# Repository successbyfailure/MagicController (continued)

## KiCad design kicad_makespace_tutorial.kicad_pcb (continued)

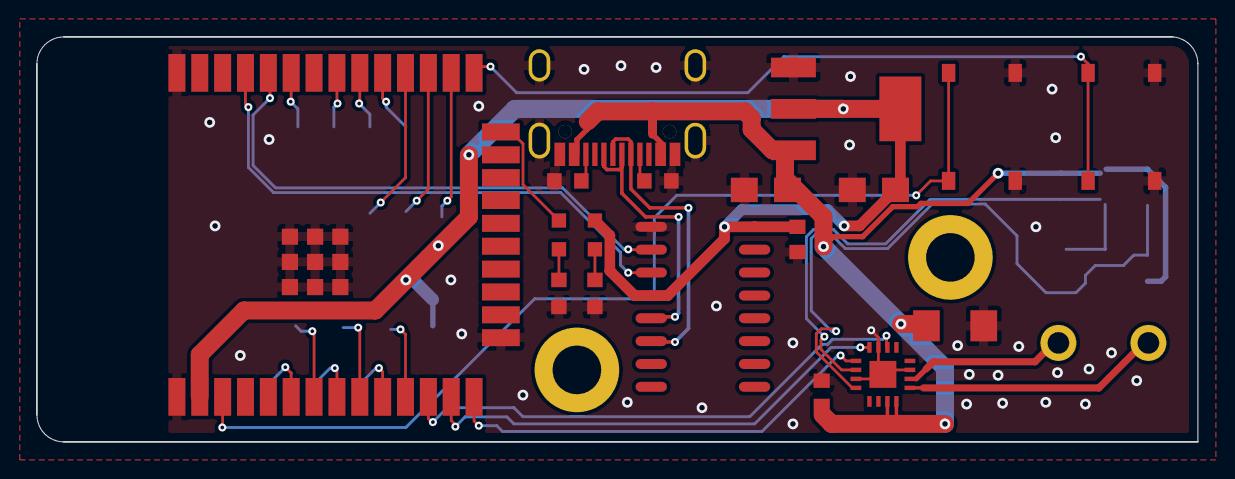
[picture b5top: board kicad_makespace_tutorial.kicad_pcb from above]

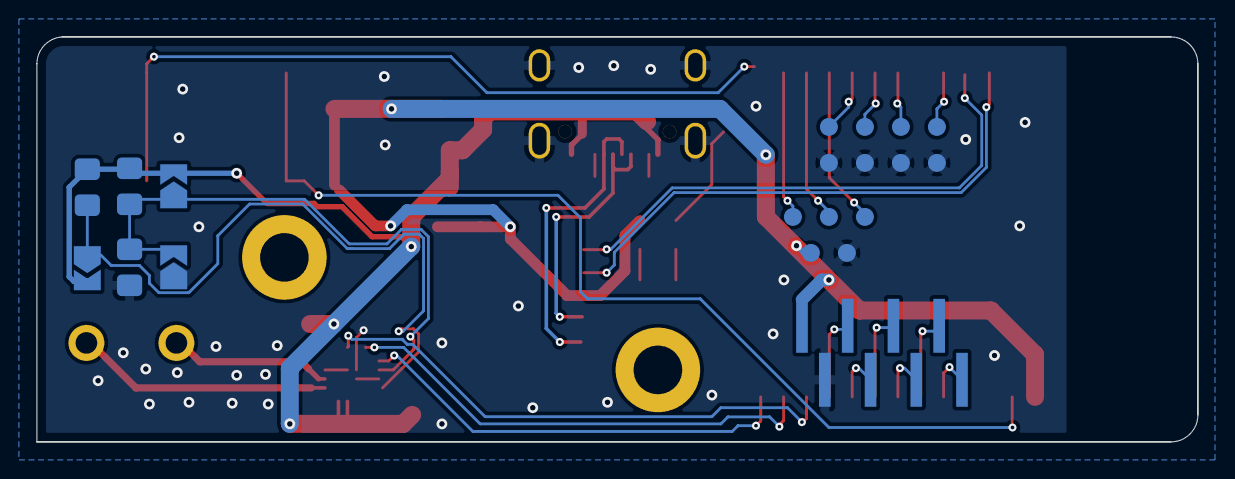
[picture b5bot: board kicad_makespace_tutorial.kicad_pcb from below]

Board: 2 copper layers, 64.5 x 22.5 mm, 41 parts (20 on the bottom side), 34 nets.

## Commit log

2024-12-31 Initial version
2024-12-31 Fab 1
2024-12-31 Add ignore files
2024-12-31 Add Readme
2024-12-31 Add images
2025-01-12 ESP32 Boilerplate
2025-01-13 Last updates
2025-01-13 Fab V1
2025-01-14 Minors
2025-01-14 RP2040 boilerplate
2025-01-20 wip
    Añadir elementos
2025-02-05 added David folder
2025-02-06 easyeda2kidad from csv
    añadido script para cargar las libs
